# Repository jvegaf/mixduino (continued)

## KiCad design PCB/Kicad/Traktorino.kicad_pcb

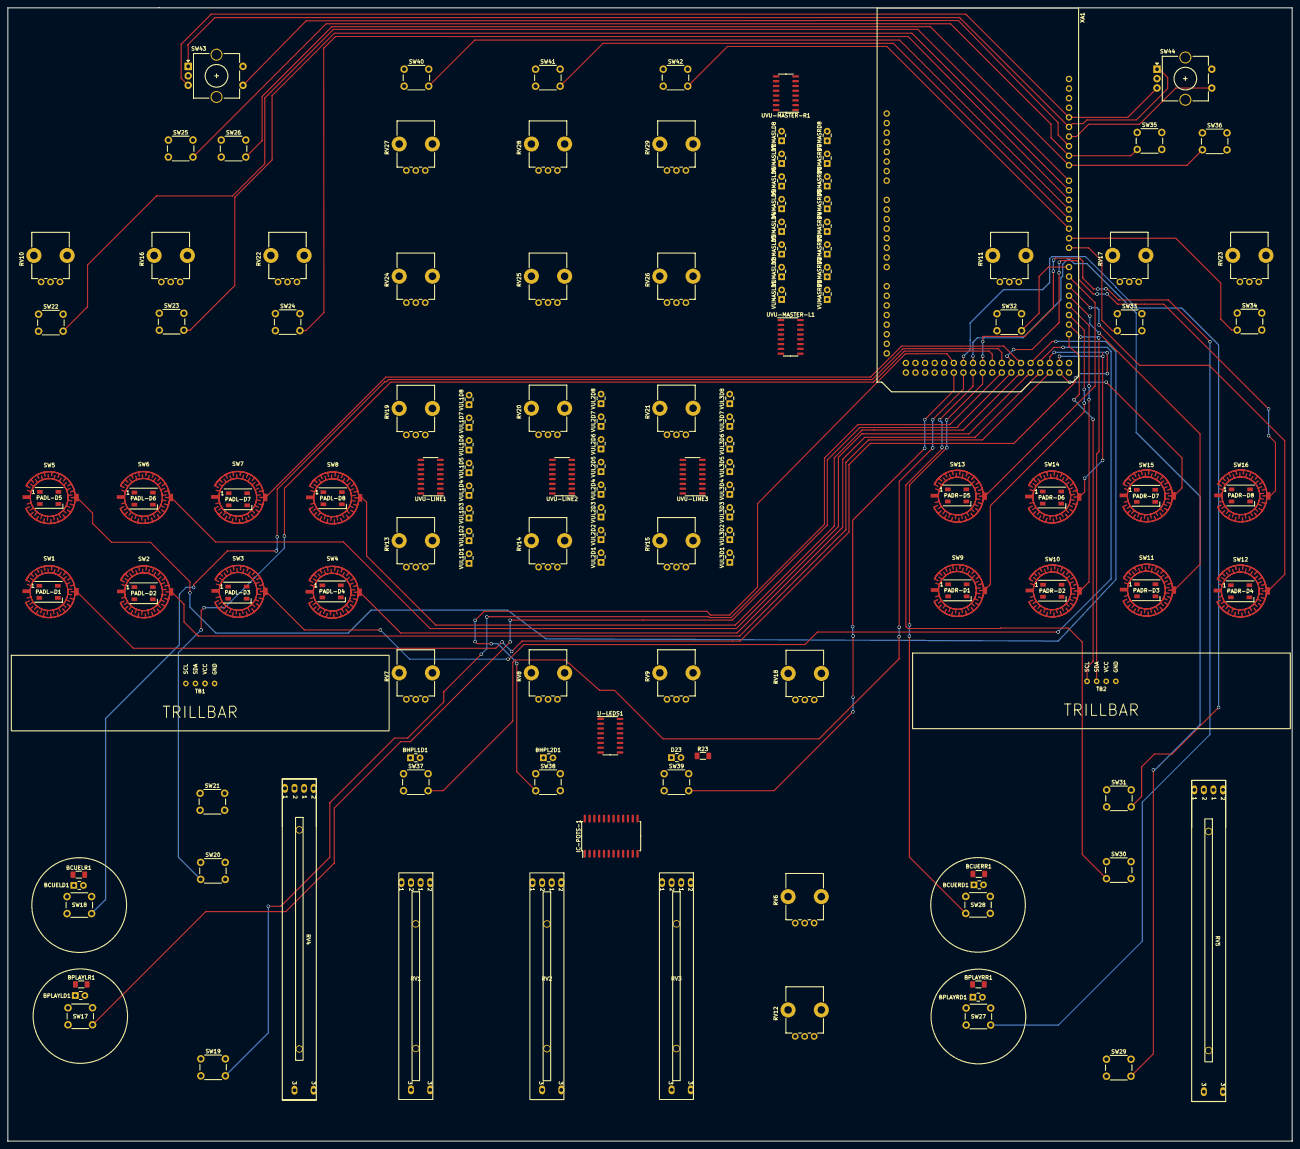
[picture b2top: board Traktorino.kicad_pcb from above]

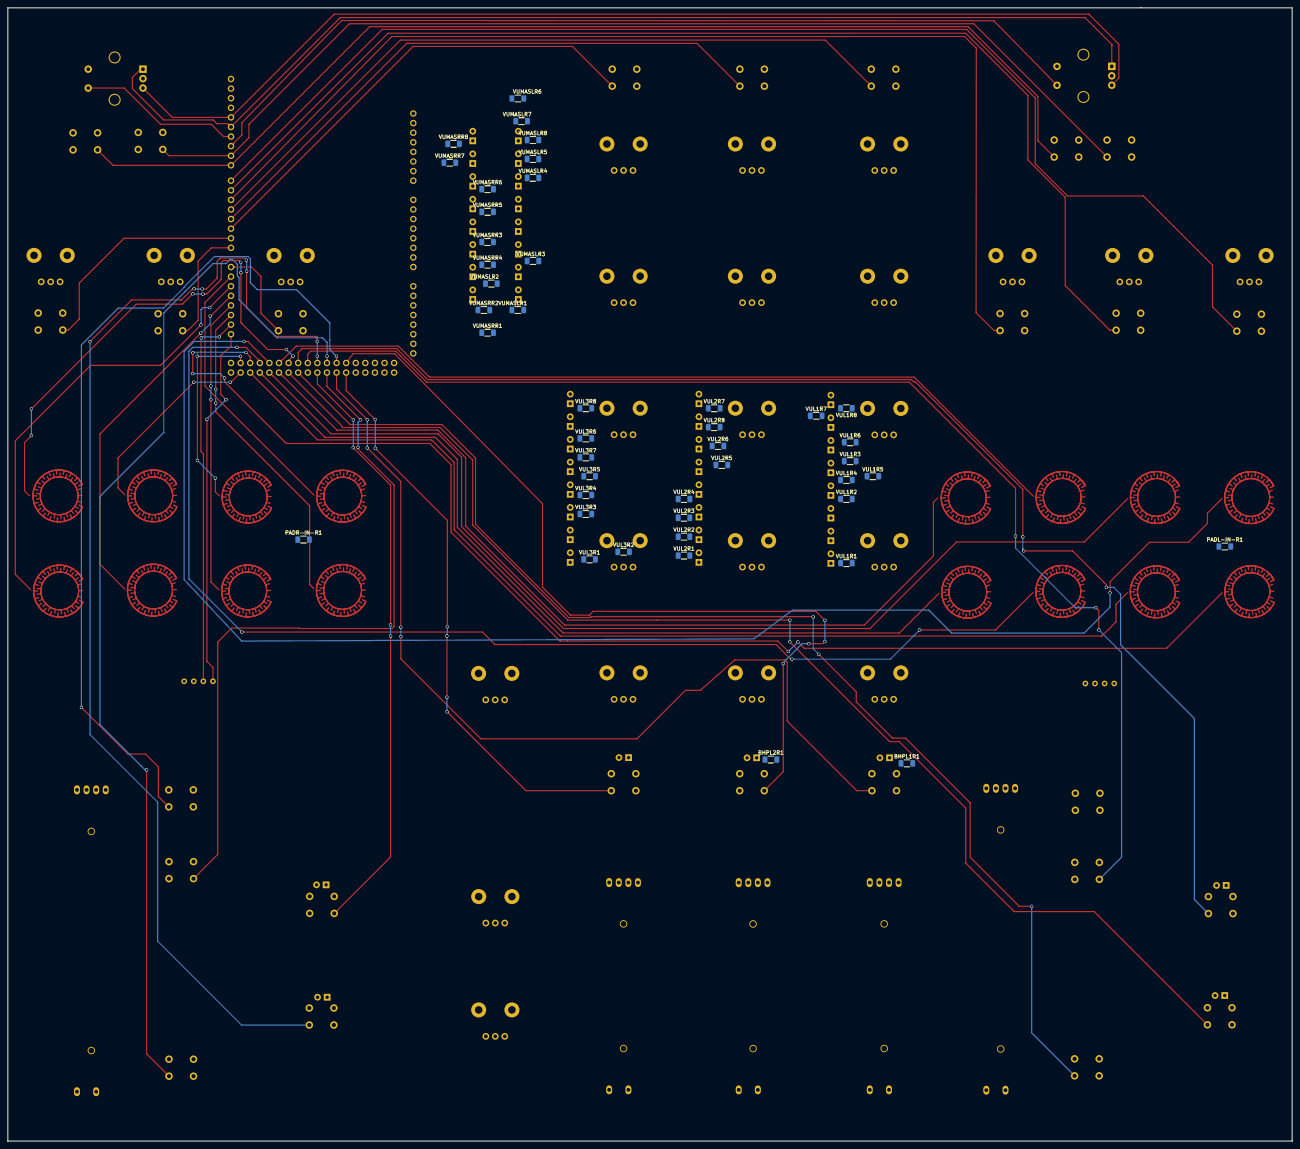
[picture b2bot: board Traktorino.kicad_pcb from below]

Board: 2 copper layers, 340.0 x 300.0 mm, 195 parts (44 on the bottom side), 201 nets.

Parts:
BCUELD1: LED_ALT; LED_Rectangular_W3.0mm_H2.0mm
BCUELR1: R_Small; R_1206_3216Metric_Pad1.30x1.75mm_HandSolder
BCUERD1: LED_ALT; LED_Rectangular_W3.0mm_H2.0mm
BCUERR1: R_Small; R_1206_3216Metric_Pad1.30x1.75mm_HandSolder
BHPL1D1, BHPL2D1: LED_ALT; LED_Rectangular_W3.0mm_H2.0mm
BHPL1R1, BHPL2R1: R_Small; R_1206_3216Metric_Pad1.30x1.75mm_HandSolder
BPLAYLD1: LED_ALT; LED_Rectangular_W3.0mm_H2.0mm
BPLAYLR1: R_Small; R_1206_3216Metric_Pad1.30x1.75mm_HandSolder
BPLAYRD1: LED_ALT; LED_Rectangular_W3.0mm_H2.0mm
BPLAYRR1: R_Small; R_1206_3216Metric_Pad1.30x1.75mm_HandSolder
D23: LED_ALT; LED_Rectangular_W3.0mm_H2.0mm
IC-POTS-1: 74HC4067D,653; SOIC-24W_7.5x15.4mm_P1.27mm
PADL-D1, PADL-D2, PADL-D3, PADL-D4, PADL-D5, PADL-D6, PADL-D7, PADL-D8: WS2812B; LED_WS2812B_PLCC4_5.0x5.0mm_P3.2mm
PADL-IN-R1: R_Small; R_1206_3216Metric_Pad1.30x1.75mm_HandSolder
PADR-D1, PADR-D2, PADR-D3, PADR-D4, PADR-D5, PADR-D6, PADR-D7, PADR-D8: WS2812B; LED_WS2812B_PLCC4_5.0x5.0mm_P3.2mm
PADR-IN-R1: R_Small; R_1206_3216Metric_Pad1.30x1.75mm_HandSolder
R23: R_Small; R_1206_3216Metric_Pad1.30x1.75mm_HandSolder
RV1: FADERL1; fader-L60
RV2: FADERL2; fader-L60
RV3: FADERL3; fader-L60
RV4: PITCH-L; fader-L75
RV5: PITH-R; fader-L75
RV6: PMIX-HP; Potentiometer_Bourns_PTV09A-1_Single_Vertical
RV7: FILTERL1; Potentiometer_Bourns_PTV09A-1_Single_Vertical
RV8: FILTERL2; Potentiometer_Bourns_PTV09A-1_Single_Vertical
RV9: FILTERL3; Potentiometer_Bourns_PTV09A-1_Single_Vertical
RV10: PFX1L; Potentiometer_Bourns_PTV09A-1_Single_Vertical
RV11: PFX1R; Potentiometer_Bourns_PTV09A-1_Single_Vertical
RV12: PVOL-HP; Potentiometer_Bourns_PTV09A-1_Single_Vertical
RV13: BASL1; Potentiometer_Bourns_PTV09A-1_Single_Vertical
RV14: BASL2; Potentiometer_Bourns_PTV09A-1_Single_Vertical
RV15: BASL3; Potentiometer_Bourns_PTV09A-1_Single_Vertical
RV16: PFX2L; Potentiometer_Bourns_PTV09A-1_Single_Vertical
RV17: PFX2R; Potentiometer_Bourns_PTV09A-1_Single_Vertical
RV18: PMASTER; Potentiometer_Bourns_PTV09A-1_Single_Vertical
RV19: MIDL1; Potentiometer_Bourns_PTV09A-1_Single_Vertical
RV20: MIDL2; Potentiometer_Bourns_PTV09A-1_Single_Vertical
RV21: MIDL3; Potentiometer_Bourns_PTV09A-1_Single_Vertical
RV22: PFX3L; Potentiometer_Bourns_PTV09A-1_Single_Vertical
RV23: PFX3R; Potentiometer_Bourns_PTV09A-1_Single_Vertical
RV24: TREL1; Potentiometer_Bourns_PTV09A-1_Single_Vertical
RV25: TREL2; Potentiometer_Bourns_PTV09A-1_Single_Vertical
RV26: TREL3; Potentiometer_Bourns_PTV09A-1_Single_Vertical
RV27: GAINL1; Potentiometer_Bourns_PTV09A-1_Single_Vertical
RV28: GAINL2; Potentiometer_Bourns_PTV09A-1_Single_Vertical
RV29: GAINL3; Potentiometer_Bourns_PTV09A-1_Single_Vertical
SW1: SWPADL1; sw-pad
SW2: SWPADL2; sw-pad
SW3: SWPADL3; sw-pad
SW4: SWPADL4; sw-pad
SW5: SWPADL5; sw-pad
SW6: SWPADL6; sw-pad
SW7: SWPADL7; sw-pad
SW8: SWPADL8; sw-pad
SW9: SWPADR1; sw-pad
SW10: SWPADR2; sw-pad
SW11: SWPADR3; sw-pad
SW12: SWPADR4; sw-pad
SW13: SWPADR5; sw-pad
SW14: SWPADR6; sw-pad
SW15: SWPADR7; sw-pad
SW16: SWPADR8; sw-pad
SW17: SWPLAYL; SW_PUSH_6mm_H5mm
SW18: SWCUEL; SW_PUSH_6mm_H5mm
SW19: SWSHIFTL; SW_PUSH_6mm_H5mm
SW20: SWSYNCL; SW_PUSH_6mm_H5mm
SW21: SWRANGEL; SW_PUSH_6mm_H5mm
SW22: SWFX1L; SW_PUSH_6mm_H5mm
SW23: SWFX2L; SW_PUSH_6mm_H5mm
SW24: SWFX3L; SW_PUSH_6mm_H5mm
SW25: SWBR-PREVL; SW_PUSH_6mm_H5mm
SW26: SWBR-BACKL; SW_PUSH_6mm_H5mm
SW27: SWPLAYR; SW_PUSH_6mm_H5mm
SW28: SWCUER; SW_PUSH_6mm_H5mm
SW29: SWSHIFTR; SW_PUSH_6mm_H5mm
SW30: SWSYNCR; SW_PUSH_6mm_H5mm
SW31: SWRANGER; SW_PUSH_6mm_H5mm
SW32: SWFX1R; SW_PUSH_6mm_H5mm
SW33: SWFX2R; SW_PUSH_6mm_H5mm
SW34: SWFX3R; SW_PUSH_6mm_H5mm
SW35: SWBR-PREVR; SW_PUSH_6mm_H5mm
SW36: SWBR-BACKR; SW_PUSH_6mm_H5mm
SW37: SWPCUEL1; SW_PUSH_6mm_H5mm
SW38: SWPCUEL2; SW_PUSH_6mm_H5mm
SW39: SWPCUEL3; SW_PUSH_6mm_H5mm
SW40: SWSEL1; SW_PUSH_6mm_H5mm
SW41: SWSEL2; SW_PUSH_6mm_H5mm
SW42: SWSEL3; SW_PUSH_6mm_H5mm
SW43: BROWSER-L; RotaryEncoder_Alps_EC11E-Switch_Vertical_H20mm_CircularMoun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
SW44: BROWSER-R; RotaryEncoder_Alps_EC11E-Switch_Vertical_H20mm_CircularMoun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
TB1: trillbar-left; trillbar
TB2: trillbar-right; trillbar
U-LEDS1: 74HC595; SO-16_3.9x9.9mm_P1.27mm
UVU-LINE1, UVU-LINE2, UVU-LINE3: 74HC595; SO-16_3.9x9.9mm_P1.27mm
UVU-MASTER-L1: 74HC595; SO-16_3.9x9.9mm_P1.27mm
UVU-MASTER-R1: 74HC595; SO-16_3.9x9.9mm_P1.27mm
VUL1D1, VUL1D2, VUL1D3, VUL1D4, VUL1D5, VUL1D6, VUL1D7, VUL1D8, VUL2D1, VUL2D2, VUL2D3, VUL2D4, VUL2D5, VUL2D6, VUL2D7, VUL2D8, VUL3D1, VUL3D2, VUL3D3, VUL3D4, VUL3D5, VUL3D6, VUL3D7, VUL3D8: LED_Filled; LED_Rectangular_W3.0mm_H2.0mm
VUL1R1, VUL1R2, VUL1R3, VUL1R4, VUL1R5, VUL1R6, VUL1R7, VUL1R8, VUL2R1, VUL2R2, VUL2R3, VUL2R4, VUL2R5, VUL2R6, VUL2R7, VUL2R8, VUL3R1, VUL3R2, VUL3R3, VUL3R4, VUL3R5, VUL3R6, VUL3R7, VUL3R8: R_Small; R_1206_3216Metric_Pad1.30x1.75mm_HandSolder
VUMASLD1, VUMASLD2, VUMASLD3, VUMASLD4, VUMASLD5, VUMASLD6, VUMASLD7, VUMASLD8: LED_Filled; LED_Rectangular_W3.0mm_H2.0mm
VUMASLR1, VUMASLR2, VUMASLR3, VUMASLR4, VUMASLR5, VUMASLR6, VUMASLR7, VUMASLR8: R_Small; R_1206_3216Metric_Pad1.30x1.75mm_HandSolder
VUMASRD1, VUMASRD2, VUMASRD3, VUMASRD4, VUMASRD5, VUMASRD6, VUMASRD7, VUMASRD8: LED_Filled; LED_Rectangular_W3.0mm_H2.0mm
VUMASRR1, VUMASRR2, VUMASRR3, VUMASRR4, VUMASRR5, VUMASRR6, VUMASRR7, VUMASRR8: R_Small; R_1206_3216Metric_Pad1.30x1.75mm_HandSolder
XA1: Arduino_Mega2560_Shield

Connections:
BAS-L1: IC-POTS-1.21 (Y10), RV13.2
BAS-L2: IC-POTS-1.20 (Y11), RV14.2
BAS-L3: IC-POTS-1.19 (Y12), RV15.2
BROWSER_A: SW43.A, SW44.A, XA1.D12
BROWSER_B: SW43.B, SW44.B, XA1.D13
FADER-L1: IC-POTS-1.8 (Y1), RV1.2
FADER-L2: IC-POTS-1.7 (Y2), RV2.2
FADER-L3: IC-POTS-1.6 (Y3), RV3.2
FILTER-L1: IC-POTS-1.2 (Y7), RV7.2
FILTER-L2: IC-POTS-1.23 (Y8), RV8.2
FILTER-L3: IC-POTS-1.22 (Y9), RV9.2
GAIN-L1: RV27.2, XA1.A1
GAIN-L2: RV28.2, XA1.A2
GAIN-L3: RV29.2, XA1.A3
GND: BCUELR1.2, BCUERR1.2, BHPL1R1.2, BHPL2R1.2, BPLAYLR1.2, BPLAYRR1.2, IC-POTS-1.12 (GND), IC-POTS-1.15 (~E), PADL-D1.3 (VSS), PADL-D2.3 (VSS), PADL-D3.3 (VSS), PADL-D4.3 (VSS), PADL-D5.3 (VSS), PADL-D6.3 (VSS), PADL-D7.3 (VSS), PADL-D8.3 (VSS), PADR-D1.3 (VSS), PADR-D2.3 (VSS), PADR-D3.3 (VSS), PADR-D4.3 (VSS), PADR-D5.3 (VSS), PADR-D6.3 (VSS), PADR-D7.3 (VSS), PADR-D8.3 (VSS), R23.2, RV1.3, RV2.3, RV3.3, RV4.3, RV5.3, RV6.3, RV7.3, RV8.3, RV9.3, RV10.3, RV11.3, RV12.3, RV13.3, RV14.3, RV15.3, RV16.3, RV17.3, RV18.3, RV19.3, RV20.3, RV21.3, RV22.3, RV23.3, RV24.3, RV25.3, RV26.3, RV27.3, RV28.3, RV29.3, SW1.1, SW2.1, SW3.1, SW4.1, SW5.1, SW6.1, SW7.1, SW8.1, SW9.1, SW10.1, SW11.1, SW12.1, SW13.1, SW14.1, SW15.1, SW16.1, SW17.1, SW18.1, SW19.1, SW20.1, SW21.1, SW22.1, SW23.1, SW24.1, SW25.1, SW26.1, SW27.1, SW28.1, SW29.1, SW30.1, SW31.1, SW32.1, SW33.1, SW34.1, SW35.1, SW36.1, SW37.1, SW38.1, SW39.1, SW40.1, SW41.1, SW42.1, SW43.C, SW43.S2, SW44.C, SW44.S2, TB1.4 (GND), TB2.4 (GND), U-LEDS1.8 (GND), U-LEDS1.13 (~OE), UVU-LINE1.8 (GND), UVU-LINE1.13 (~OE), UVU-LINE2.8 (GND), UVU-LINE2.13 (~OE), UVU-LINE3.8 (GND), UVU-LINE3.13 (~OE), UVU-MASTER-L1.8 (GND), UVU-MASTER-L1.13 (~OE), UVU-MASTER-R1.8 (GND), UVU-MASTER-R1.13 (~OE), VUL1R1.2, VUL1R2.2, VUL1R3.2, VUL1R4.2, VUL1R5.2, VUL1R6.2, VUL1R7.2, VUL1R8.2, VUL2R1.2, VUL2R2.2, VUL2R3.2, VUL2R4.2, VUL2R5.2, VUL2R6.2, VUL2R7.2, VUL2R8.2, VUL3R1.2, VUL3R2.2, VUL3R3.2, VUL3R4.2, VUL3R5.2, VUL3R6.2, VUL3R7.2, VUL3R8.2, VUMASLR1.2, VUMASLR2.2, VUMASLR3.2, VUMASLR4.2, VUMASLR5.2, VUMASLR6.2, VUMASLR7.2, VUMASLR8.2, VUMASRR1.2, VUMASRR2.2, VUMASRR3.2, VUMASRR4.2, VUMASRR5.2, VUMASRR6.2, VUMASRR7.2, VUMASRR8.2, XA1.GND1 (GND), XA1.GND2 (GND), XA1.GND3 (GND), XA1.GND5 (GND), XA1.GND6 (GND)
LEDCUEL: BCUELD1.2 (A), U-LEDS1.4 (QE)
LEDCUER: BCUERD1.2 (A), U-LEDS1.2 (QC)
LEDHPL1: BHPL1D1.2 (A), U-LEDS1.7 (QH)
LEDHPL2: BHPL2D1.2 (A), U-LEDS1.6 (QG)
LEDHPL3: D23.2 (A), U-LEDS1.5 (QF)
LEDPLAYL: BPLAYLD1.2 (A), U-LEDS1.3 (QD)
LEDPLAYR: BPLAYRD1.2 (A), U-LEDS1.1 (QB)
MID-L1: IC-POTS-1.18 (Y13), RV19.2
MID-L2: IC-POTS-1.17 (Y14), RV20.2
MID-L3: IC-POTS-1.16 (Y15), RV21.2
MPLEX-A0: IC-POTS-1.1 (Z), XA1.A0
MPLEX-S0: IC-POTS-1.10 (S0), XA1.D48
MPLEX-S1: IC-POTS-1.11 (S1), XA1.D49
MPLEX-S2: IC-POTS-1.14 (S2), XA1.D50
MPLEX-S3: IC-POTS-1.13 (S3), XA1.D51
unnamed: BCUELD1.1 (K), BCUELR1.1
unnamed: BCUERD1.1 (K), BCUERR1.1
unnamed: BHPL1D1.1 (K), BHPL1R1.1
unnamed: BHPL2D1.1 (K), BHPL2R1.1
unnamed: BPLAYLD1.1 (K), BPLAYLR1.1
unnamed: BPLAYRD1.1 (K), BPLAYRR1.1
unnamed: D23.1 (K), R23.1
unnamed: PADL-D1.2 (DOUT), PADL-D2.4 (DIN)
unnamed: PADL-D1.4 (DIN), PADL-IN-R1.2
unnamed: PADL-D2.2 (DOUT), PADL-D3.4 (DIN)
unnamed: PADL-D3.2 (DOUT), PADL-D4.4 (DIN)
unnamed: PADL-D4.2 (DOUT), PADL-D5.4 (DIN)
unnamed: PADL-D5.2 (DOUT), PADL-D6.4 (DIN)
unnamed: PADL-D6.2 (DOUT), PADL-D7.4 (DIN)
unnamed: PADL-D7.2 (DOUT), PADL-D8.4 (DIN)
unnamed: PADR-D1.2 (DOUT), PADR-D2.4 (DIN)
unnamed: PADR-D1.4 (DIN), PADR-IN-R1.2
unnamed: PADR-D2.2 (DOUT), PADR-D3.4 (DIN)
unnamed: PADR-D3.2 (DOUT), PADR-D4.4 (DIN)
unnamed: PADR-D4.2 (DOUT), PADR-D5.4 (DIN)
unnamed: PADR-D5.2 (DOUT), PADR-D6.4 (DIN)
unnamed: PADR-D6.2 (DOUT), PADR-D7.4 (DIN)
unnamed: PADR-D7.2 (DOUT), PADR-D8.4 (DIN)
unnamed: U-LEDS1.14 (SER), UVU-MASTER-R1.9 (QH')
unnamed: UVU-LINE1.9 (QH'), UVU-LINE2.14 (SER)
unnamed: UVU-LINE2.9 (QH'), UVU-LINE3.14 (SER)
unnamed: UVU-LINE3.9 (QH'), UVU-MASTER-L1.14 (SER)
unnamed: UVU-MASTER-L1.9 (QH'), UVU-MASTER-R1.14 (SER)
unnamed: VUL1D1.1 (K), VUL1R1.1
unnamed: VUL1D2.1 (K), VUL1R2.1
unnamed: VUL1D3.1 (K), VUL1R3.1
unnamed: VUL1D4.1 (K), VUL1R4.1
unnamed: VUL1D5.1 (K), VUL1R5.1
unnamed: VUL1D6.1 (K), VUL1R6.1
unnamed: VUL1D7.1 (K), VUL1R7.1
unnamed: VUL1D8.1 (K), VUL1R8.1
unnamed: VUL2D1.1 (K), VUL2R1.1
unnamed: VUL2D2.1 (K), VUL2R2.1
unnamed: VUL2D3.1 (K), VUL2R3.1
unnamed: VUL2D4.1 (K), VUL2R4.1
unnamed: VUL2D5.1 (K), VUL2R5.1
unnamed: VUL2D6.1 (K), VUL2R6.1
unnamed: VUL2D7.1 (K), VUL2R7.1
unnamed: VUL2D8.1 (K), VUL2R8.1
unnamed: VUL3D1.1 (K), VUL3R1.1
unnamed: VUL3D2.1 (K), VUL3R2.1
unnamed: VUL3D3.1 (K), VUL3R3.1
unnamed: VUL3D4.1 (K), VUL3R4.1
unnamed: VUL3D5.1 (K), VUL3R5.1
unnamed: VUL3D6.1 (K), VUL3R6.1
unnamed: VUL3D7.1 (K), VUL3R7.1
unnamed: VUL3D8.1 (K), VUL3R8.1
unnamed: VUMASLD1.1 (K), VUMASLR1.1
unnamed: VUMASLD2.1 (K), VUMASLR2.1
unnamed: VUMASLD3.1 (K), VUMASLR3.1
unnamed: VUMASLD4.1 (K), VUMASLR4.1
unnamed: VUMASLD5.1 (K), VUMASLR5.1
unnamed: VUMASLD6.1 (K), VUMASLR6.1
unnamed: VUMASLD7.1 (K), VUMASLR7.1
unnamed: VUMASLD8.1 (K), VUMASLR8.1
unnamed: VUMASRD1.1 (K), VUMASRR1.1
unnamed: VUMASRD2.1 (K), VUMASRR2.1
unnamed: VUMASRD3.1 (K), VUMASRR3.1
unnamed: VUMASRD4.1 (K), VUMASRR4.1
unnamed: VUMASRD5.1 (K), VUMASRR5.1
unnamed: VUMASRD6.1 (K), VUMASRR6.1
unnamed: VUMASRD7.1 (K), VUMASRR7.1
unnamed: VUMASRD8.1 (K), VUMASRR8.1
PFX-1L: RV10.2, XA1.A7
PFX-1R: RV11.2, XA1.A10
PFX-2L: RV16.2, XA1.A8
PFX-2R: RV17.2, XA1.A11
PFX-3L: RV22.2, XA1.A9
PFX-3R: RV23.2, XA1.A12
PITCH-L: IC-POTS-1.9 (Y0), RV4.2
PITCH-R: IC-POTS-1.3 (Y6), RV5.2
PMASTER: RV18.2, XA1.A13
PMIX-HP: IC-POTS-1.5 (Y4), RV6.2
PVOL-HP: IC-POTS-1.4 (Y5), RV12.2
SCL: TB1.1 (SCL), TB2.1 (SCL), XA1.D21 (D21_SCL)
SDA: TB1.2 (SDA), TB2.2 (SDA), XA1.D20 (D20_SDA)
SF-CLOCK: U-LEDS1.11 (SRCLK), UVU-LINE1.11 (SRCLK), UVU-LINE2.11 (SRCLK), UVU-LINE3.11 (SRCLK), UVU-MASTER-L1.11 (SRCLK), UVU-MASTER-R1.11 (SRCLK), XA1.D52
SF-DATA: UVU-LINE1.14 (SER), XA1.A15
SF-LATCH: U-LEDS1.12 (RCLK), UVU-LINE1.12 (RCLK), UVU-LINE2.12 (RCLK), UVU-LINE3.12 (RCLK), UVU-MASTER-L1.12 (RCLK), UVU-MASTER-R1.12 (RCLK), XA1.D53 (D53_SS)
SIG_PAD_LED_L: PADL-IN-R1.1, PADR-IN-R1.1, XA1.D46
SWBR-BACK: SW26.2, SW36.2, XA1.D8
SWBR-PREVIEW: SW25.2, SW35.2, XA1.D9
SWCUE-L: SW18.2, XA1.D34
SWCUE-R: SW28.2, XA1.D39
SWFX1-L: SW22.2, XA1.D7
SWFX1-R: SW32.2, XA1.D14 (D14_TX3)
SWFX2-L: SW23.2, XA1.D6
SWFX2-R: SW33.2, XA1.D0 (D0_RX0)
SWFX3-L: SW24.2, XA1.D5
SWFX3-R: SW34.2, XA1.D1 (D1_TX0)
SWPAD-L1: SW1.2, XA1.D24
SWPAD-L2: SW2.2, XA1.D25
SWPAD-L3: SW3.2, XA1.D26
SWPAD-L4: SW4.2, XA1.D27
SWPAD-L5: SW5.2, XA1.D28
SWPAD-L6: SW6.2, XA1.D29
SWPAD-L7: SW7.2, XA1.D30
SWPAD-L8: SW8.2, XA1.D31
SWPAD-R1: SW9.2, XA1.D19 (D19_RX1)
SWPAD-R2: SW10.2, XA1.D18 (D18_TX1)
SWPAD-R3: SW11.2, XA1.D17 (D17_RX2)
SWPAD-R4: SW12.2, XA1.D16 (D16_TX2)
SWPAD-R5: SW13.2, XA1.D15 (D15_RX3)
SWPAD-R6: SW14.2, XA1.D22
SWPAD-R7: SW15.2, XA1.D23
SWPAD-R8: SW16.2, XA1.D32
SWPLAY-L: SW17.2, XA1.D33
SWPLAY-R: SW27.2, XA1.D38
SWPRECUE-L1: SW37.2, XA1.D43
SWPRECUE-L2: SW38.2, XA1.D44
SWPRECUE-L3: SW39.2, XA1.D45
SWRANGE-L: SW21.2, XA1.D37
SWRANGE-R: SW31.2, XA1.D42
SWSEL-L1: SW40.2, XA1.D4
SWSEL-L2: SW41.2, XA1.D3 (D3_INT1)
SWSEL-L3: SW42.2, XA1.D2 (D2_INT0)
SWSHIFT-L: SW19.2, XA1.D35
SWSHIFT-R: SW29.2, XA1.D40
SWSYNC-L: SW20.2, XA1.D36
SWSYNC-R: SW30.2, XA1.D41
SW_BROWSER_L: SW43.S1, XA1.D10
SW_BROWSER_R: SW44.S1, XA1.D11
TRE-L1: RV24.2, XA1.A4
TRE-L2: RV25.2, XA1.A5
TRE-L3: RV26.2, XA1.A6
VCC: IC-POTS-1.24 (VCC), PADL-D1.1 (VDD), PADL-D2.1 (VDD), PADL-D3.1 (VDD), PADL-D4.1 (VDD), PADL-D5.1 (VDD), PADL-D6.1 (VDD), PADL-D7.1 (VDD), PADL-D8.1 (VDD), PADR-D1.1 (VDD), PADR-D2.1 (VDD), PADR-D3.1 (VDD), PADR-D4.1 (VDD), PADR-D5.1 (VDD), PADR-D6.1 (VDD), PADR-D7.1 (VDD), PADR-D8.1 (VDD), RV1.1, RV2.1, RV3.1, RV4.1, RV5.1, RV6.1, RV7.1, RV8.1, RV9.1, RV10.1, RV11.1, RV12.1, RV13.1, RV14.1, RV15.1, RV16.1, RV17.1, RV18.1, RV19.1, RV20.1, RV21.1, RV22.1, RV23.1, RV24.1, RV25.1, RV26.1, RV27.1, RV28.1, RV29.1, TB1.3 (VCC), TB2.3 (VCC), U-LEDS1.10 (~SRCLR), U-LEDS1.16 (VCC), UVU-LINE1.10 (~SRCLR), UVU-LINE1.16 (VCC), UVU-LINE2.10 (~SRCLR), UVU-LINE2.16 (VCC), UVU-LINE3.10 (~SRCLR), UVU-LINE3.16 (VCC), UVU-MASTER-L1.10 (~SRCLR), UVU-MASTER-L1.16 (VCC), UVU-MASTER-R1.10 (~SRCLR), UVU-MASTER-R1.16 (VCC), XA1.5V1 (5V), XA1.5V3 (5V), XA1.5V4 (5V)
VUL1-0: UVU-LINE1.15 (QA), VUL1D1.2 (A)
VUL1-1: UVU-LINE1.1 (QB), VUL1D2.2 (A)
VUL1-2: UVU-LINE1.2 (QC), VUL1D3.2 (A)
VUL1-3: UVU-LINE1.3 (QD), VUL1D4.2 (A)
VUL1-4: UVU-LINE1.4 (QE), VUL1D5.2 (A)
VUL1-5: UVU-LINE1.5 (QF), VUL1D6.2 (A)
VUL1-6: UVU-LINE1.6 (QG), VUL1D7.2 (A)
VUL1-7: UVU-LINE1.7 (QH), VUL1D8.2 (A)
VUL2-0: UVU-LINE2.15 (QA), VUL2D1.2 (A)
VUL2-1: UVU-LINE2.1 (QB), VUL2D2.2 (A)
VUL2-2: UVU-LINE2.2 (QC), VUL2D3.2 (A)
VUL2-3: UVU-LINE2.3 (QD), VUL2D4.2 (A)
VUL2-4: UVU-LINE2.4 (QE), VUL2D5.2 (A)
VUL2-5: UVU-LINE2.5 (QF), VUL2D6.2 (A)
VUL2-6: UVU-LINE2.6 (QG), VUL2D7.2 (A)
VUL2-7: UVU-LINE2.7 (QH), VUL2D8.2 (A)
VUL3-0: UVU-LINE3.15 (QA), VUL3D1.2 (A)
VUL3-1: UVU-LINE3.1 (QB), VUL3D2.2 (A)
VUL3-2: UVU-LINE3.2 (QC), VUL3D3.2 (A)
VUL3-3: UVU-LINE3.3 (QD), VUL3D4.2 (A)
VUL3-4: UVU-LINE3.4 (QE), VUL3D5.2 (A)
VUL3-5: UVU-LINE3.5 (QF), VUL3D6.2 (A)
VUL3-6: UVU-LINE3.6 (QG), VUL3D7.2 (A)
VUL3-7: UVU-LINE3.7 (QH), VUL3D8.2 (A)
VUMASL-0: UVU-MASTER-L1.15 (QA), VUMASLD1.2 (A)
VUMASL-1: UVU-MASTER-L1.1 (QB), VUMASLD2.2 (A)
VUMASL-2: UVU-MASTER-L1.2 (QC), VUMASLD3.2 (A)
VUMASL-3: UVU-MASTER-L1.3 (QD), VUMASLD4.2 (A)
VUMASL-4: UVU-MASTER-L1.4 (QE), VUMASLD5.2 (A)
VUMASL-5: UVU-MASTER-L1.5 (QF), VUMASLD6.2 (A)
VUMASL-6: UVU-MASTER-L1.6 (QG), VUMASLD7.2 (A)
VUMASL-7: UVU-MASTER-L1.7 (QH), VUMASLD8.2 (A)
VUMASR-0: UVU-MASTER-R1.15 (QA), VUMASRD1.2 (A)
VUMASR-1: UVU-MASTER-R1.1 (QB), VUMASRD2.2 (A)
VUMASR-2: UVU-MASTER-R1.2 (QC), VUMASRD3.2 (A)
VUMASR-3: UVU-MASTER-R1.3 (QD), VUMASRD4.2 (A)
VUMASR-4: UVU-MASTER-R1.4 (QE), VUMASRD5.2 (A)
VUMASR-5: UVU-MASTER-R1.5 (QF), VUMASRD6.2 (A)
VUMASR-6: UVU-MASTER-R1.6 (QG), VUMASRD7.2 (A)
VUMASR-7: UVU-MASTER-R1.7 (QH), VUMASRD8.2 (A)

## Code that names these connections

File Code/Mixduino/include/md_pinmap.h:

#pragma once

#ifndef MD_PINMAP_H
#define MD_PINMAP_H
#include <Arduino.h>


//////////////////////////////////////
// BUTTONS
uint8_t const SWFXR_2      = 4;
uint8_t const SWFXR_3      = 5;
uint8_t const SWFXL_1      = 8;
uint8_t const SW_BROWSER_R = 7;
uint8_t const SW_BROWSER_L = 10;
uint8_t const SWFXL_2      = 9;
uint8_t const SWFXL_3      = 11;
uint8_t const SWFXR_1      = 12;
uint8_t const SWBR_PREVIEW = 14;
uint8_t const SWBR_BACK    = 15;

const uint8_t aSwSet[]     = {
    SWFXR_2,
    SWFXR_3,
    SWFXL_1,
    SW_BROWSER_R,
    SW_BROWSER_L,
    SWFXL_2,
    SWFXL_3,
    SWFXR_1,
    SWBR_PREVIEW,
    SWBR_BACK
};

const uint8_t nASw         = 10;

uint8_t const L_BROWSER_A  = 2;
uint8_t const L_BROWSER_B  = 3;
uint8_t const NP_DATA      = 6;
uint8_t const L1VU_LATCH   = 16;
uint8_t const L1VU_SIG     = 17;
uint8_t const R_BROWSER_B  = 18;
uint8_t const R_BROWSER_A  = 19;
uint8_t const MRVU_LATCH   = 26;
uint8_t const MRVU_SIG     = 28;
uint8_t const MLVU_LATCH   = 30;
uint8_t const L2VU_SIG     = 31;
uint8_t const MLVU_SIG     = 32;
uint8_t const L3VU_SIG     = 34;
uint8_t const L3VU_LATCH   = 36;
uint8_t const FBL_LATCH    = 37;
uint8_t const L2VU_LATCH   = 38;
uint8_t const FBL_SIG      = 39;
uint8_t const FBR_LATCH    = 42;
uint8_t const FBR_SIG      = 44;
uint8_t const SRCLK        = 52;

//////////////////////////////////////
// MULTIPLEXER

uint8_t const MPLEX_S0     = 47;
uint8_t const MPLEX_S1     = 49;
uint8_t const MPLEX_S2     = 40;
uint8_t const MPLEX_S3     = 53;
uint8_t const MPLEX_A1     = A1;
uint8_t const MPLEX_A2     = A2;
uint8_t const MPLEX_A3     = A3;
uint8_t const MPLEX_A4     = A4;

const uint8_t MUX_PINS[]    = {
    MPLEX_S0,
    MPLEX_S1,
    MPLEX_S2,
    MPLEX_S3
};

//////////////////////////////////////
// POTS ANALOG PINS

uint8_t const PFXR_1       = A0;
uint8_t const PMASTER      = A14;

const uint8_t aPotsSet[]   = {
    PFXR_1,
    PMASTER
};

const uint8_t nAPots       = 2;

#endif

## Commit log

2021-03-16 Schematic housekeeping
2021-03-24 labels wip
2021-03-24 labelss wip
2021-03-24 labels end
2021-03-24 Labels orientation
2021-03-25 SHIFT REGS
2021-03-26 layout update
2021-03-26 SCHEMA UPD
2021-03-26 temp
2021-03-27 multiplexers and vumeters
2021-03-27 more sheets
    pots
    vumeters
    switchers
2021-03-28 multiplexers WIP
2021-03-28 change to kicad nightly
2021-03-28 update elements WIP
2021-03-29 progress
2021-03-30 mod layout
2021-03-30 Arduino mega retrofit WIP
2021-03-31 pad footprint updated
2021-04-01 trillbar added
2021-04-02 board updated
2021-04-02 placed 3d model components
2021-04-03 housekeeping
2021-04-04 fixing 3dmodels
2021-04-04 midi images
2021-04-05 retoques
2021-04-05 lib fix
2021-04-11 2 vumeters test
2021-04-11 change few pins and programming
2021-04-12 neopixel lib
2021-04-13 change code to platformio
2021-04-14 update gitignore
2021-04-19 shift register concepts
2021-04-21 funciona con dos registros
2021-04-21 extract to class
2021-04-21 little refactor
2021-04-22 redesign
2021-04-23 technical drawing
2021-04-24 sr wip
2021-04-25 routing
2021-04-26 more routing
2021-04-27 removed neopixel capacitors
2021-04-27 gerbers
2021-04-29 neopixels library concept
2021-04-30 Design mistake fixed
    - changed D0 & D1 pins asign
    - progress on main code
2021-04-30 temp env
2021-05-01 shift register module finished
2021-05-01 mistake fixed
    added another latch pin for feedback leds SReg.
2021-05-02 SRegs and NPixels modules WIP
2021-05-02 neopixels module completed
2021-05-02 buttons module
2021-05-03 pots module completed
2021-05-03 firmware dual boot
2021-05-04 neopixels module manage changed
2021-05-04 npixel model
2021-05-04 npixels works !!!
2021-05-05 vumeters works !
2021-05-16 Auto stash before checking out "HEAD"
2021-05-17 bug fix
2021-05-22 refactor
2021-05-22 udpates
2021-05-31 shifter libr to feedback leds
2021-06-02 pruebas
2021-06-05 schematic updated
2021-06-10 tracking WIP
2021-06-11 windows 0 errors
2021-06-12 Rev5 completed
2021-06-12 hotfix gerbers
2021-06-12 silkscreen udpated
2021-06-13 version comment
2021-06-13 refactor pinmaps
2021-06-13 works
2021-06-17 some changes
    - put all neopixels together in one line. First left leds, last right leds.
    - change left fx2 fx3 buttons funtions to left browser inputs
2021-06-17 updated traktor settings file
2021-06-18 all neopixels together
2021-06-18 enclosure top
2021-06-18 STEP file
2021-06-26 Enclosure
2021-06-26 pinset refactor
2021-07-07 trill pruebas
2021-07-09 Enclouser dxfs
2021-07-10 left trillbar works
2021-07-13 all touchbars & encoders works
2021-07-13 refactor encoder and more mapping
2021-07-16 new render
2021-07-16 dxf top enclosure
2021-07-18 3D Button Models
2021-07-23 refactor models
2021-07-23 update render
2021-07-28 refactor pots
2021-07-29 added draws of 3d model buttons in pcb [WIP]
2021-07-29 position holes for btns
2021-07-29 changed encoders pins to interrupt pins
2021-07-30 refactor main file
2021-09-03 adding ics WIP
2021-09-04 SCHEMATIC FINISHED
2021-09-04 added transistor and 3x leds play- cue
2021-09-05 routing WIP
2021-09-05 routes done
2021-09-05 shematic pdf and step model board
2021-09-05 update models
2021-09-06 renders
2021-09-06 update renders top back
2021-09-10 user drawings done
2021-09-11 top cover
2021-09-14 change vu wip
2021-09-21 routes finished
2021-09-21 update gerbers
2021-09-22 fix gerbers
2021-09-25 maps modified
2021-09-25 potkit refactored
2021-09-25 btnkit refactored
2021-09-25 mdcore refactored
2021-09-26 update schematic
2021-09-26 modified trillbar connectors
2021-09-26 60mm pot 3dmodel changed
2021-09-28 top-cover updated
2021-09-28 trillbars
2021-09-29 enclosure freecad model
2021-09-29 update model
2021-09-30 modeling
2021-10-08 Bottom Cover refactored
2021-10-09 render
2021-10-10 render done
2021-10-12 mux prueba
2021-10-13 Fixed Buttons Read implementation
2021-10-13 typo fix
2021-10-16 midi changes
2021-10-26 more progress
2021-10-28 advance WIP
2021-10-29 more prog
2021-10-31 last changes
2021-11-01 move btns read to mdcore
2021-11-01 muxer refactor
2021-11-01 npkit refactor
2021-11-02 PadSw
2021-11-04 Np pads
2021-11-04 remove extern enums
2021-11-05 core refactor
2021-11-05 Feedback leds
2021-11-05 check mode previously
2021-11-05 ugly fix
2021-11-07 big refactor
2021-11-07 member props
2021-11-07 Hotfix
2021-11-07 success build
2021-11-09 Bugfixes
2021-11-10 set initialdeck B [WIP]
2021-11-10 refactor to simplify pads
2021-11-10 update color set
2021-11-10 changed pad pixels from note to control
2021-11-25 traktor tsi
2021-11-26 modeling pots
2021-11-27 mixer and other features
2021-11-29 add namespaces
2021-11-29 event handler
2021-11-30 refactor encoder & button
2021-11-30 mux button refactored
2021-12-02 pots refactor
2021-12-02 touchbar refactor
2021-12-02 update config
2021-12-02 bugfix
2021-12-02 big refactor with domain events
2021-12-02 check flags
2021-12-03 rename
2021-12-03 domain modeling WIP
2021-12-04 remove note off handler
2021-12-07 the most big refactor ever seen XDDD
2021-12-07 renaming
2021-12-07 muxerPots
2021-12-08 potd
2021-12-08 added positions
2021-12-08 pad refactor
2021-12-08 Auto stash before merge of "firm8" and "origin/firm8"
2021-12-08 callback
2021-12-09 core refactored
2021-12-09 changs
2021-12-11 update deck calls
2021-12-11 buttons works well, but pot doesn't work
2022-01-25 TSI updated
2022-02-08 ignore local history
2022-02-08 modularize encoder
2022-03-07 mixxx controller WIP
2022-08-05 added touchkit to namespace
2022-08-05 midi values
2022-08-06 update tsi
2022-08-06 refactor to namespaces
2022-08-08 refactor midi btns
2022-08-08 pads colors
2022-08-15 refactor wip
2022-08-15 build works
2022-08-16 Create LICENSE
